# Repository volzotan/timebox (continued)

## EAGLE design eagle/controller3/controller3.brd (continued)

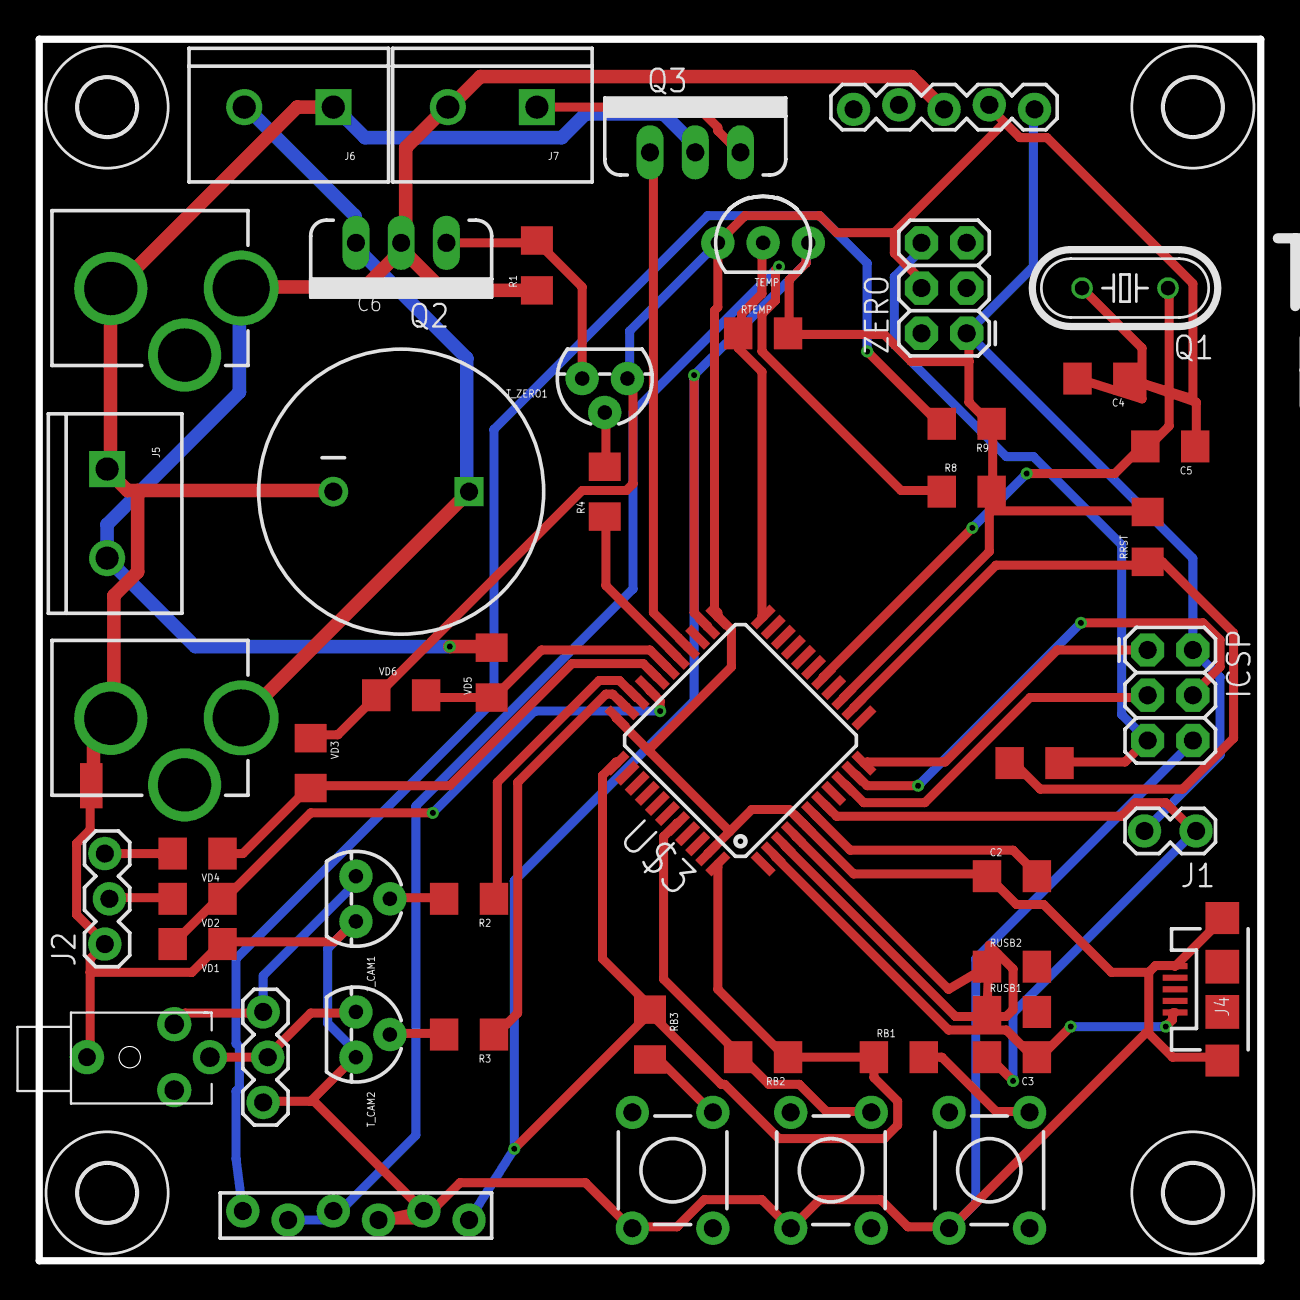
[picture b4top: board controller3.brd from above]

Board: 2 copper layers, 68.6 x 68.6 mm, 55 parts (0 on the bottom side), 44 nets.

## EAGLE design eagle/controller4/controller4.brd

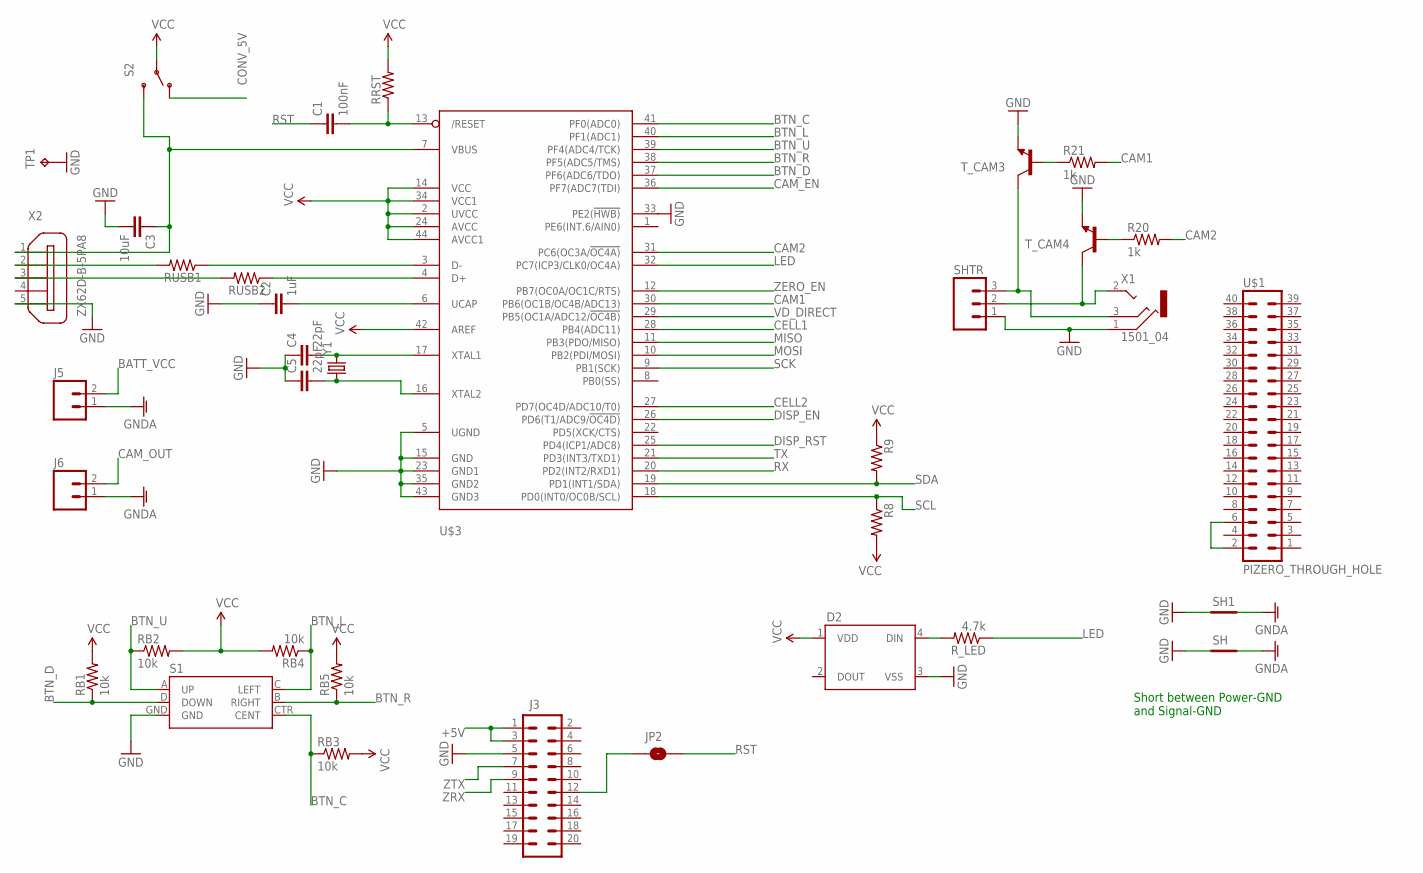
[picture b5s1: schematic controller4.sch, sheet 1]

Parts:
C1: 100nF; 1206
C2: 1uF; 1206
C3: 10uF; 1206
C4, C5: 22pF; 1206
D2: WS2812B
J3: M10X2; 2X10
J5, J6: M023.5MM_LOCK; SCREWTERMINAL-3.5MM-2_LOCK
JP2: JUMPER-PAD-2-NOYES_SILK; PAD-JUMPER-2-NO_YES_SILK
R8, R9: RESISTOR1206; 1206
R20, R21: 1k; 1206
RB1, RB2, RB3, RB4, RB5: 10k; 1206
RRST: RESISTOR1206; 1206
RUSB1, RUSB2: RESISTOR1206; 1206
R_LED: 4.7k; 1206
S1: JOYSTICK_MINI
S2: SWITCH-SPDTPTH_LOCK; SWITCH-SPDT_LOCK.007S
SH, SH1: SHORT-HT5; SHORT_TOP-50
SHTR: M03LOCK; 1X03_LOCK
TP1: TPB1,27; B1,27
T_CAM3, T_CAM4: TRANSISTOR_NPN2N3904; TO-92
U$1: PIZERO_THROUGH_HOLE; PIZERO_THOUGH_HOLE
U$3: ATMEGA32U4-AU; TQFP44
X1: 1501_04; 1501_05
X2: ZX62D-B-5PA8
Y1: CRYSTALHC49US; HC49US

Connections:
+5V: J3.1, J3.3; also elsewhere on the board
BATT_VCC: J5.2; also elsewhere on the board
BTN_C: RB3.1, S1.CTR (CENT), U$3.41 (PF0(ADC0))
BTN_D: RB1.1, S1.D (DOWN), U$3.37 (PF6(ADC6/TDO))
BTN_L: RB4.1, S1.C (LEFT), U$3.40 (PF1(ADC1))
BTN_R: RB5.1, S1.B (RIGHT), U$3.38 (PF5(ADC5/TMS))
BTN_U: RB2.1, S1.A (UP), U$3.39 (PF4(ADC4/TCK))
CAM1: R21.2, U$3.30 (PB6(OC1B/OC4B/ADC13))
CAM2: R20.2, U$3.31 (PC6(OC3A/!OC4A))
CAM_EN: U$3.36 (PF7(ADC7(TDI)); also elsewhere on the board
CAM_OUT: J6.2; also elsewhere on the board
CELL1: U$3.28 (PB4(ADC11)); also elsewhere on the board
CELL2: U$3.27 (PD7(OC4D/ADC10/T0)); also elsewhere on the board
CONV_5V: S2.1 (O); also elsewhere on the board
DISP_EN: U$3.26 (PD6(T1/ADC9/!OC4D)); also elsewhere on the board
DISP_RST: U$3.25 (PD4(ICP1/ADC8)); also elsewhere on the board
GND: C2.1, C3.2, C4.1, C5.1, D2.3 (VSS), J3.5, S1.GND, SH.1, SH1.1, SHTR.1, TP1.TP, T_CAM3.1 (E), T_CAM4.1 (E), U$3.5 (UGND), U$3.15 (GND), U$3.23 (GND1), U$3.33 (PE2(!HWB)), U$3.35 (GND2), U$3.43 (GND3), X1.1, X2.5; also elsewhere on the board
GNDA: J5.1, J6.1, SH.2, SH1.2
LED: R_LED.1, U$3.32 (PC7(ICP3/CLK0/OC4A))
MISO: U$3.11 (PB3(PDO/MISO)); also elsewhere on the board
MOSI: U$3.10 (PB2(PDI/MOSI)); also elsewhere on the board
unnamed: C1.2, RRST.1, U$3.13 (/RESET)
unnamed: RUSB1.1, U$3.3 (D-)
unnamed: RUSB2.1, U$3.4 (D+)
unnamed: D2.4 (DIN), R_LED.2
unnamed: C4.2, U$3.17 (XTAL1), Y1.2
unnamed: C5.2, U$3.16 (XTAL2), Y1.1
unnamed: RUSB1.2, X2.2
unnamed: RUSB2.2, X2.3
unnamed: J3.12, JP2.1
unnamed: U$1.2, U$1.6
unnamed: C2.2, U$3.6 (UCAP)
unnamed: C3.1, S2.3 (S), U$3.7 (VBUS), X2.1
unnamed: R21.1, T_CAM3.2 (B)
unnamed: SHTR.2, T_CAM4.3 (C), X1.2
unnamed: SHTR.3, T_CAM3.3 (C), X1.3
unnamed: R20.1, T_CAM4.2 (B)
RST: C1.1, JP2.2; also elsewhere on the board
RX: U$3.20 (PD2(INT2/RXD1)); also elsewhere on the board
SCK: U$3.9 (PB1(SCK)); also elsewhere on the board
SCL: R8.1, U$3.18 (PD0(INT0/OC0B/SCL)); also elsewhere on the board
SDA: R9.2, U$3.19 (PD1(INT1/SDA)); also elsewhere on the board
TX: U$3.21 (PD3(INT3/TXD1)); also elsewhere on the board
VCC: D2.1 (VDD), R8.2, R9.1, RB1.2, RB2.2, RB3.2, RB4.2, RB5.2, RRST.2, S2.2, U$3.2 (UVCC), U$3.14 (VCC), U$3.24 (AVCC), U$3.34 (VCC1), U$3.42 (AREF), U$3.44 (AVCC1); also elsewhere on the board
VD_DIRECT: U$3.29 (PB5(OC1A/ADC12/!OC4B)); also elsewhere on the board
ZERO_EN: U$3.12 (PB7(OC0A/OC1C/RTS)); also elsewhere on the board
ZRX: J3.9; also elsewhere on the board
ZTX: J3.7; also elsewhere on the board

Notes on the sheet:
Short between Power-GND and Signal-GND

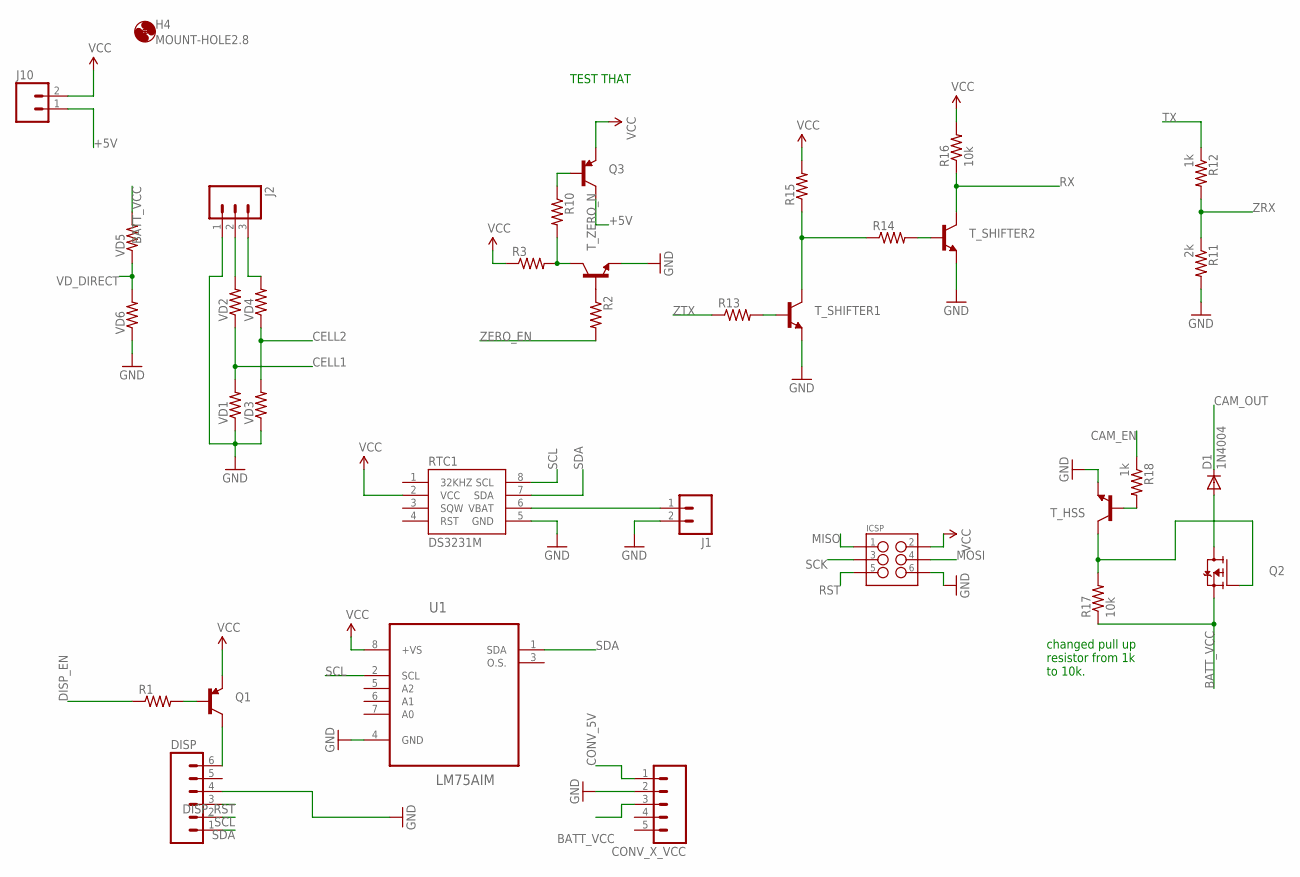
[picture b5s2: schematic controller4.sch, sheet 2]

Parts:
CONV_X_VCC: M05LOCK; 1X05_LOCK
D1: 1N4004; DO41-10
DISP: M06FEMALE_LOCK; 1X06_FEMALE_LOCK.010
H4: MOUNT-HOLE2.8; 2,8
ICSP: M03X2FEMALE; 2X3
J1: M02LOCK_LONGPADS; 1X02_LOCK_LONGPADS
J2: M03LOCK; 1X03_LOCK
J10: M02LOCK; 1X02_LOCK
Q1, Q3: TRANSISTOR_PNPTO92; TO-92
Q2: FDD4141TO252; TO252
R1, R2, R3, R10, R13, R14, R15: RESISTOR1206; 1206
R11: 2k; 1206
R12, R18: 1k; 1206
R16, R17: 10k; 1206
RTC1: DS3231M; SOIC8
T_HSS: TRANSISTOR_NPN2N3904; TO-92
T_SHIFTER1, T_SHIFTER2: TRANSISTOR_NPN2N3904; TO-92
T_ZERO_N: TRANSISTOR_NPN2N3904; TO-92
U1: LM75AIM; SOIC127P620X175-8N
VD1, VD2, VD3, VD4, VD5, VD6: RESISTOR1206; 1206

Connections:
+5V: J10.1, Q3.3 (C); also elsewhere on the board
BATT_VCC: CONV_X_VCC.3, Q2.2 (S), R17.1, VD5.2; also elsewhere on the board
CAM_EN: R18.1; also elsewhere on the board
CAM_OUT: D1.C; also elsewhere on the board
CELL1: VD1.2, VD2.1; also elsewhere on the board
CELL2: VD3.2, VD4.1; also elsewhere on the board
CONV_5V: CONV_X_VCC.1; also elsewhere on the board
DISP_EN: R1.1; also elsewhere on the board
DISP_RST: DISP.3; also elsewhere on the board
GND: CONV_X_VCC.2, DISP.4, ICSP.6, J1.2, J2.1, R11.2, RTC1.5 (GND), T_HSS.1 (E), T_SHIFTER1.1 (E), T_SHIFTER2.1 (E), T_ZERO_N.1 (E), U1.4 (GND), VD1.1, VD3.1, VD6.1; also elsewhere on the board
MISO: ICSP.1; also elsewhere on the board
MOSI: ICSP.4; also elsewhere on the board
unnamed: J2.3, VD4.2
unnamed: J2.2, VD2.2
unnamed: DISP.6, Q1.3 (C)
unnamed: Q1.2 (B), R1.2
unnamed: R2.1, T_ZERO_N.2 (B)
unnamed: Q3.2 (B), R10.1
unnamed: D1.A, Q2.3 (D)
unnamed: R13.2, T_SHIFTER1.2 (B)
unnamed: R3.2, R10.2, T_ZERO_N.3 (C)
unnamed: R14.1, R15.1, T_SHIFTER1.3 (C)
unnamed: R14.2, T_SHIFTER2.2 (B)
unnamed: R18.2, T_HSS.2 (B)
unnamed: Q2.1 (G), R17.2, T_HSS.3 (C)
RST: ICSP.5; also elsewhere on the board
RX: R16.1, T_SHIFTER2.3 (C); also elsewhere on the board
SCK: ICSP.3; also elsewhere on the board
SCL: DISP.2, RTC1.8 (SCL), U1.2 (SCL); also elsewhere on the board
SDA: DISP.1, RTC1.7 (SDA), U1.1 (SDA); also elsewhere on the board
TX: R12.1; also elsewhere on the board
VBAT: J1.1, RTC1.6 (VBAT)
VCC: ICSP.2, J10.2, Q1.1 (E), Q3.1 (E), R3.1, R15.2, R16.2, RTC1.2 (VCC), U1.8 (+VS); also elsewhere on the board
VD_DIRECT: VD5.1, VD6.2; also elsewhere on the board
ZERO_EN: R2.2; also elsewhere on the board
ZRX: R11.1, R12.2; also elsewhere on the board
ZTX: R13.1; also elsewhere on the board

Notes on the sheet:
TEST THAT
changed pull up resistor from 1k to 10k.

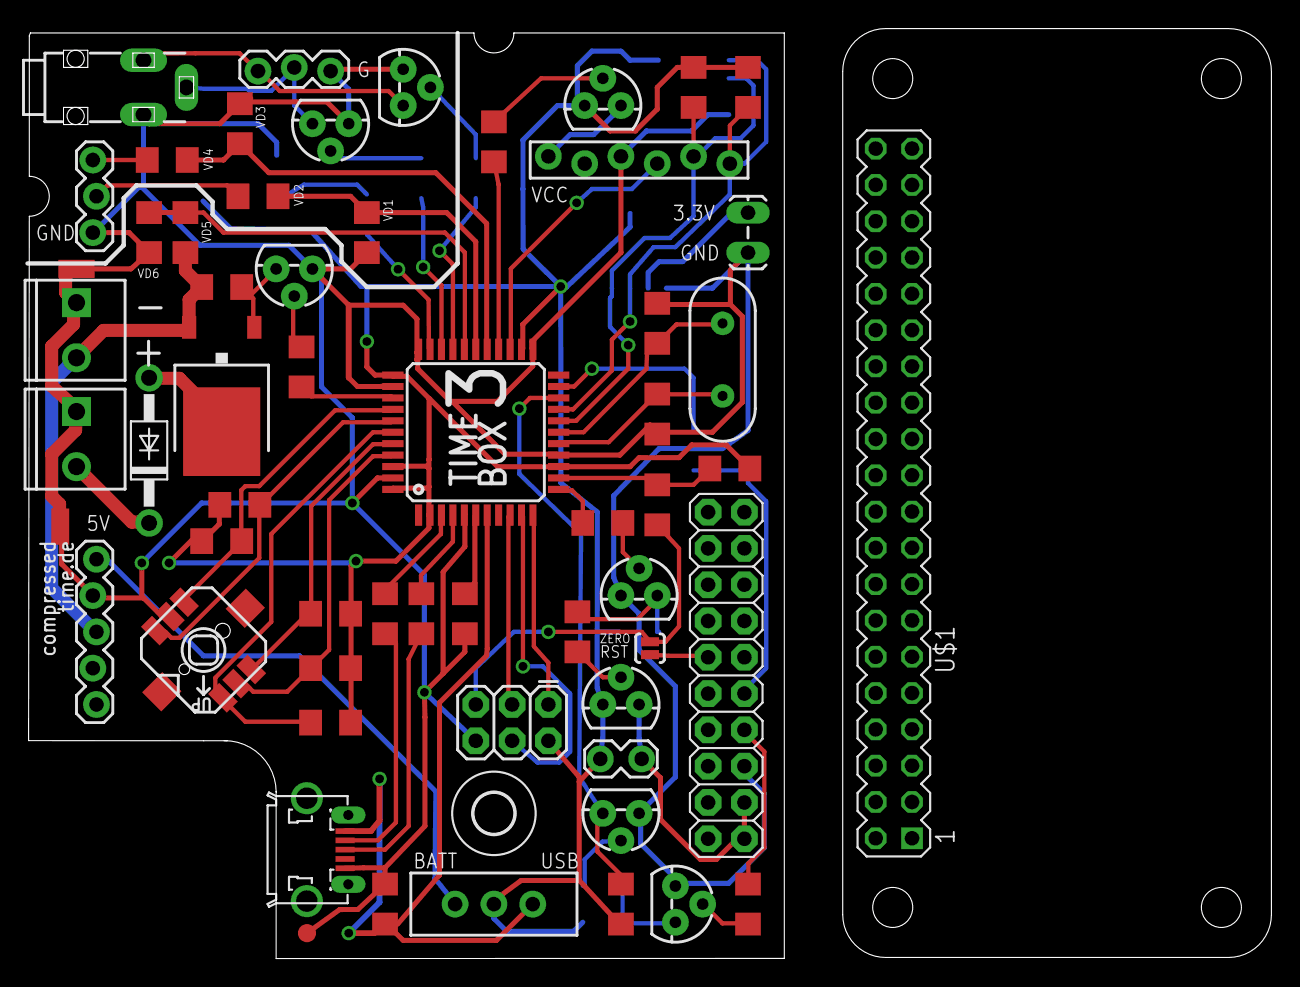
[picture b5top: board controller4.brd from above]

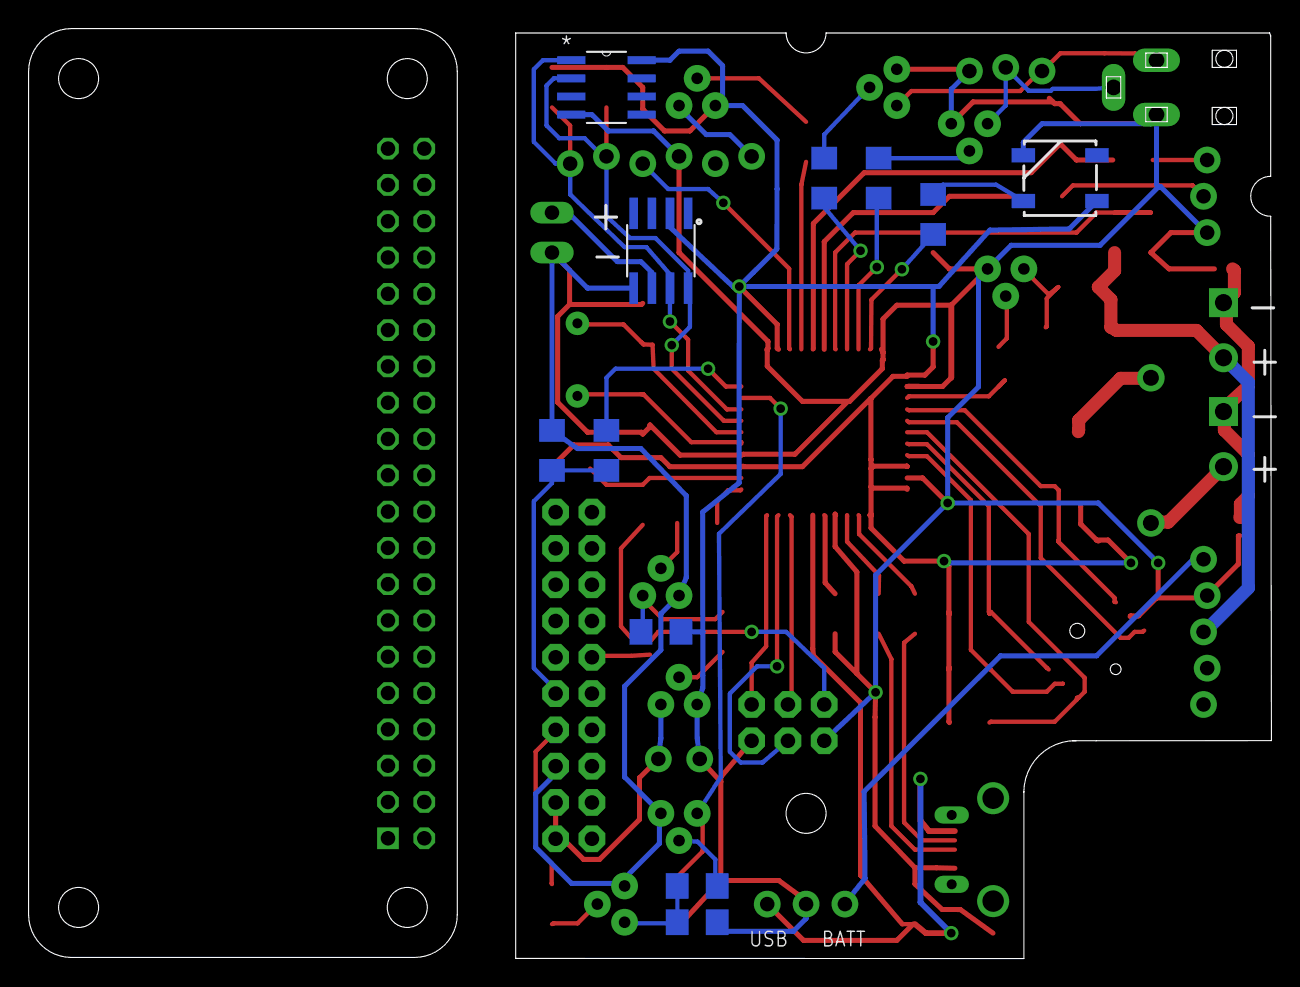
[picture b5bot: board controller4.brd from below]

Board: 2 copper layers, 52.9 x 64.8 mm, 71 parts (11 on the bottom side), 62 nets.

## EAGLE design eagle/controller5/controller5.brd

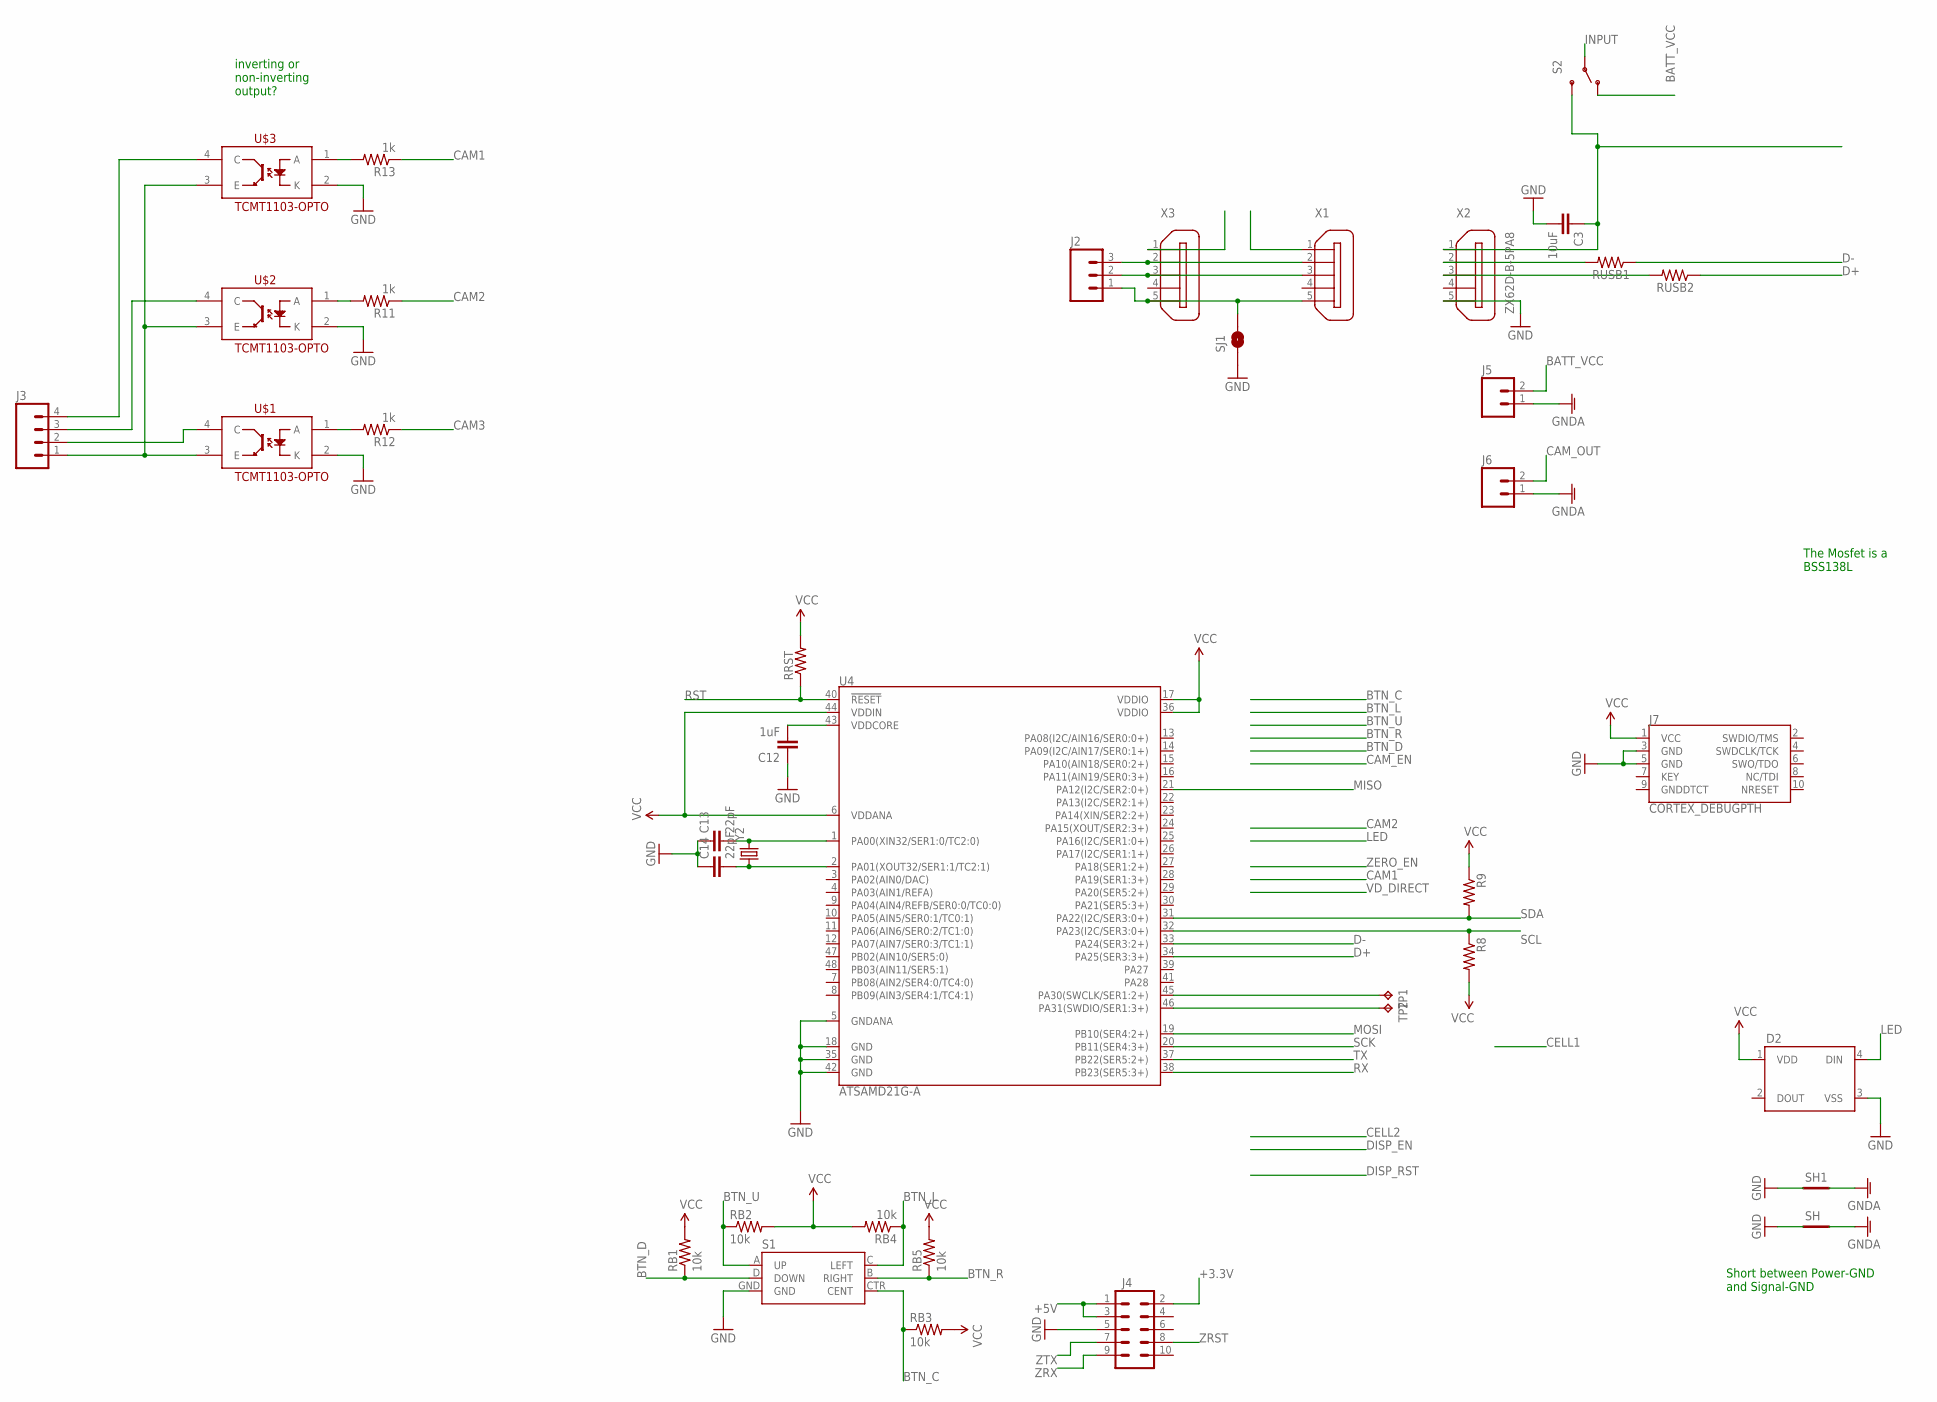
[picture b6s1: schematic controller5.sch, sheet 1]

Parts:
C3: 10uF; 1206
C12: 1uF; 1206
C13, C14: 22pF; 1206
D2: WS2812B
J2: M03LOCK; 1X03_LOCK
J3: M04LOCK; 1X04_LOCK
J4: M05X2NO_SILK; 2X5_NOSILK
J5, J6: M023.5MM_LOCK; SCREWTERMINAL-3.5MM-2_LOCK
J7: CORTEX_DEBUGPTH; 2X5-PTH-1.27MM
R8, R9: RESISTOR1206; 1206
R11, R12, R13: 1k; 1206
RB1, RB2, RB3, RB4, RB5: 10k; 1206
RRST: RESISTOR1206; 1206
RUSB1, RUSB2: RESISTOR1206; 1206
S1: JOYSTICK_MINI
S2: SWITCH-SPDTPTH_LOCK; SWITCH-SPDT_LOCK.007S
SH, SH1: SHORT-HT5; SHORT_TOP-50
SJ1: SOLDERJUMPERNO; SJ_2S-NO
TP1, TP2: TPTP20R; TP20R
U4: ATSAMD21G-A; TQFP-48
U$1, U$2, U$3: TCMT1103-OPTO; SSOP-4
X1, X2, X3: ZX62D-B-5PA8
Y2: CRYSTALCRYSTAL-SMD-5X3-16MHZ; CRYSTAL-SMD-5X3

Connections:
+3.3V: J4.2
+5V: J4.1, J4.3
BATT_VCC: J5.2, S2.1 (O); also elsewhere on the board
BTN_C: RB3.1, S1.CTR (CENT)
BTN_D: RB1.1, S1.D (DOWN)
BTN_L: RB4.1, S1.C (LEFT)
BTN_R: RB5.1, S1.B (RIGHT)
BTN_U: RB2.1, S1.A (UP)
CAM1: R13.1
CAM2: R11.1
CAM3: R12.1
CAM_OUT: J6.2; also elsewhere on the board
D+: RUSB2.1, U4.34 (PA25(SER3:3+))
D-: RUSB1.1, U4.33 (PA24(SER3:2+))
GND: C3.2, C12.1, C13.1, C14.1, D2.3 (VSS), J4.5, J7.3 (GND), J7.5 (GND), S1.GND, SH.1, SH1.1, SJ1.1, U4.5 (GNDANA), U4.18 (GND), U4.35 (GND), U4.42 (GND), U$1.2 (K), U$2.2 (K), U$3.2 (K), X2.5; also elsewhere on the board
GNDA: J5.1, J6.1, SH.2, SH1.2
INPUT: S2.2; also elsewhere on the board
LED: D2.4 (DIN)
MISO: U4.21 (PA12(I2C/SER2:0+))
MOSI: U4.19 (PB10(SER4:2+))
unnamed: TP1.TP, U4.45 (PA30(SWCLK/SER1:2+))
unnamed: TP2.TP, U4.46 (PA31(SWDIO/SER1:3+))
unnamed: J2.3, X1.2, X3.2
unnamed: J2.2, X1.3, X3.3
unnamed: J2.1, SJ1.2, X1.5, X3.5
unnamed: R11.2, U$2.1 (A)
unnamed: R12.2, U$1.1 (A)
unnamed: RUSB1.2, X2.2
unnamed: RUSB2.2, X2.3
unnamed: J3.1, U$1.3 (E), U$2.3 (E), U$3.3 (E)
unnamed: C3.1, S2.3 (S), X2.1
unnamed: C12.2, U4.43 (VDDCORE)
unnamed: R13.2, U$3.1 (A)
unnamed: C13.2, U4.1 (PA00(XIN32/SER1:0/TC2:0)), Y2.3 (2)
unnamed: C14.2, U4.2 (PA01(XOUT32/SER1:1/TC2:1)), Y2.1
unnamed: J3.2, U$1.4 (C)
unnamed: J3.3, U$2.4 (C)
unnamed: J3.4, U$3.4 (C)
RST: RRST.1, U4.40 (!RESET!)
RX: U4.38 (PB23(SER5:3+))
SCK: U4.20 (PB11(SER4:3+))
SCL: R8.1, U4.32 (PA23(I2C/SER3:0+)); also elsewhere on the board
SDA: R9.2, U4.31 (PA22(I2C/SER3:0+)); also elsewhere on the board
TX: U4.37 (PB22(SER5:2+))
VCC: D2.1 (VDD), J7.1 (VCC), R8.2, R9.1, RB1.2, RB2.2, RB3.2, RB4.2, RB5.2, RRST.2, U4.6 (VDDANA), U4.17 (VDDIO), U4.36 (VDDIO), U4.44 (VDDIN); also elsewhere on the board
ZRST: J4.8
ZRX: J4.9
ZTX: J4.7

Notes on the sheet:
Short between Power-GND and Signal-GND
The Mosfet is a BSS138L
inverting or non-inverting output?

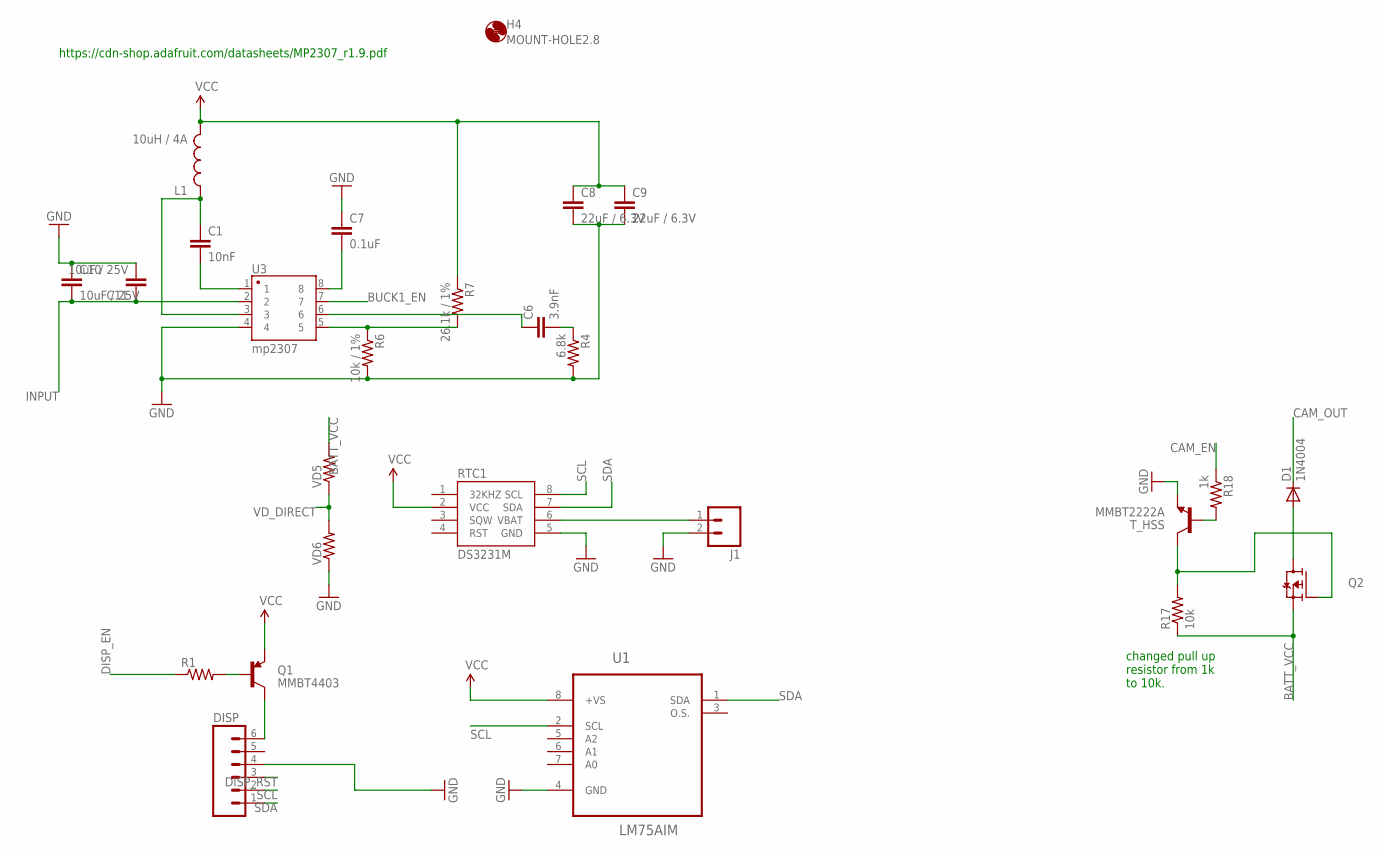
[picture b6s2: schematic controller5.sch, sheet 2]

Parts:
C1: 10nF; 1206
C6: 3.9nF; 1206
C7: 0.1uF; 1206
C8, C9: 22uF / 6.3V; 1206
C10, C11: 10uF / 25V; 1206
D1: 1N4004; DO41-10
DISP: M06FEMALE_LOCK; 1X06_FEMALE_LOCK.010
H4: MOUNT-HOLE2.8; 2,8
J1: M02LOCK_LONGPADS; 1X02_LOCK_LONGPADS
L1: 10uH / 4A; SDR0403
Q1: MMBT4403; SOT23-3
Q2: FDD4141TO252; TO252
R1: RESISTOR1206; 1206
R4: 6.8k; 1206
R6: 10k / 1%; 1206
R7: 26.1k / 1%; 1206
R17: 10k; 1206
R18: 1k; 1206
RTC1: DS3231M; SOIC8
T_HSS: MMBT2222A; SOT23-3
U1: LM75AIM; SOIC127P620X175-8N
U3: mp2307; SO08-UNIVERSAL
VD5, VD6: RESISTOR1206; 1206

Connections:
BATT_VCC: Q2.2 (S), R17.1, VD5.2; also elsewhere on the board
BUCK1_EN: U3.7
CAM_EN: R18.1
CAM_OUT: D1.C; also elsewhere on the board
DISP_EN: R1.1
DISP_RST: DISP.3
GND: C7.1, C8.2, C9.2, C10.1, C11.2, DISP.4, J1.2, R4.2, R6.2, RTC1.5 (GND), T_HSS.2 (E), U1.4 (GND), U3.4, VD6.1; also elsewhere on the board
INPUT: C10.2, C11.1, U3.2; also elsewhere on the board
unnamed: C1.1, L1.P$1 (1), U3.3
unnamed: DISP.6, Q1.3 (C)
unnamed: Q1.1 (B), R1.2
unnamed: C1.2, U3.1
unnamed: D1.A, Q2.3 (D)
unnamed: C7.2, U3.8
unnamed: R6.1, R7.2, U3.5
unnamed: C6.1, U3.6
unnamed: C6.2, R4.1
unnamed: R18.2, T_HSS.1 (B)
unnamed: Q2.1 (G), R17.2, T_HSS.3 (C)
SCL: DISP.2, RTC1.8 (SCL), U1.2 (SCL); also elsewhere on the board
SDA: DISP.1, RTC1.7 (SDA), U1.1 (SDA); also elsewhere on the board
VBAT: J1.1, RTC1.6 (VBAT)
VCC: C8.1, C9.1, L1.P$2 (2), Q1.2 (E), R7.1, RTC1.2 (VCC), U1.8 (+VS); also elsewhere on the board
VD_DIRECT: VD5.1, VD6.2

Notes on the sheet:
changed pull up resistor from 1k to 10k.
https://cdn-shop.adafruit.com/datasheets/MP2307_r1.9.pdf

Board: 2 copper layers, 66 parts (0 on the bottom side), 48 nets, no tracks yet.

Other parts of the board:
H3: MOUNT-HOLE2.8; 2,8
